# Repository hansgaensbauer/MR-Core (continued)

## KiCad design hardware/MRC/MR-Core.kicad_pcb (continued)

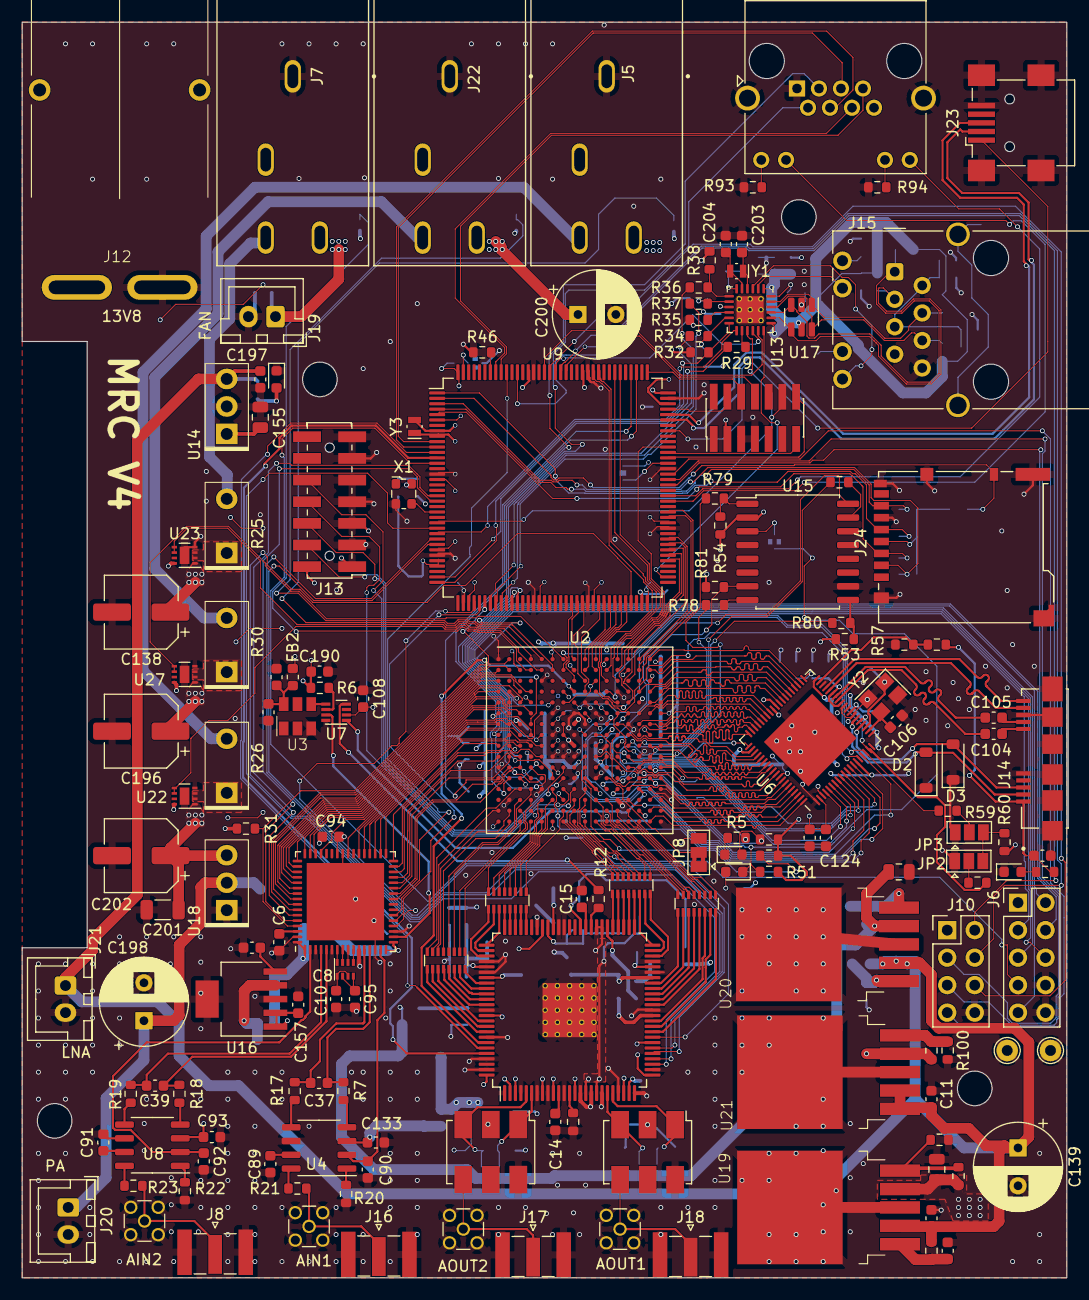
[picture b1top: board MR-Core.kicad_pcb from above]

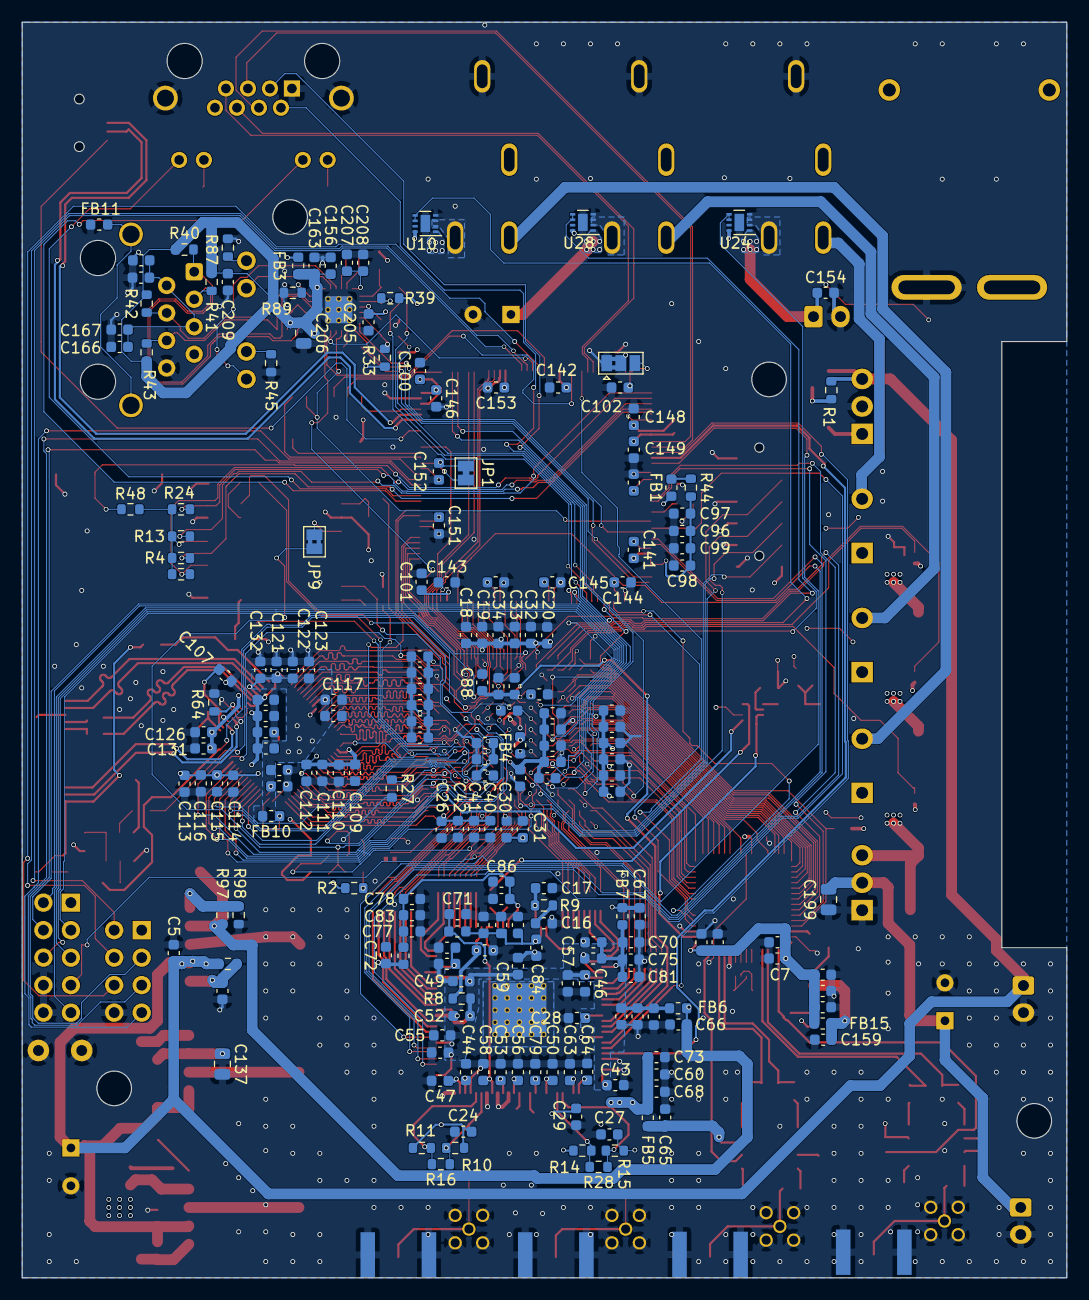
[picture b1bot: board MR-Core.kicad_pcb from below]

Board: 4 copper layers, 96.5 x 116.0 mm, 360 parts (203 on the bottom side), 377 nets.

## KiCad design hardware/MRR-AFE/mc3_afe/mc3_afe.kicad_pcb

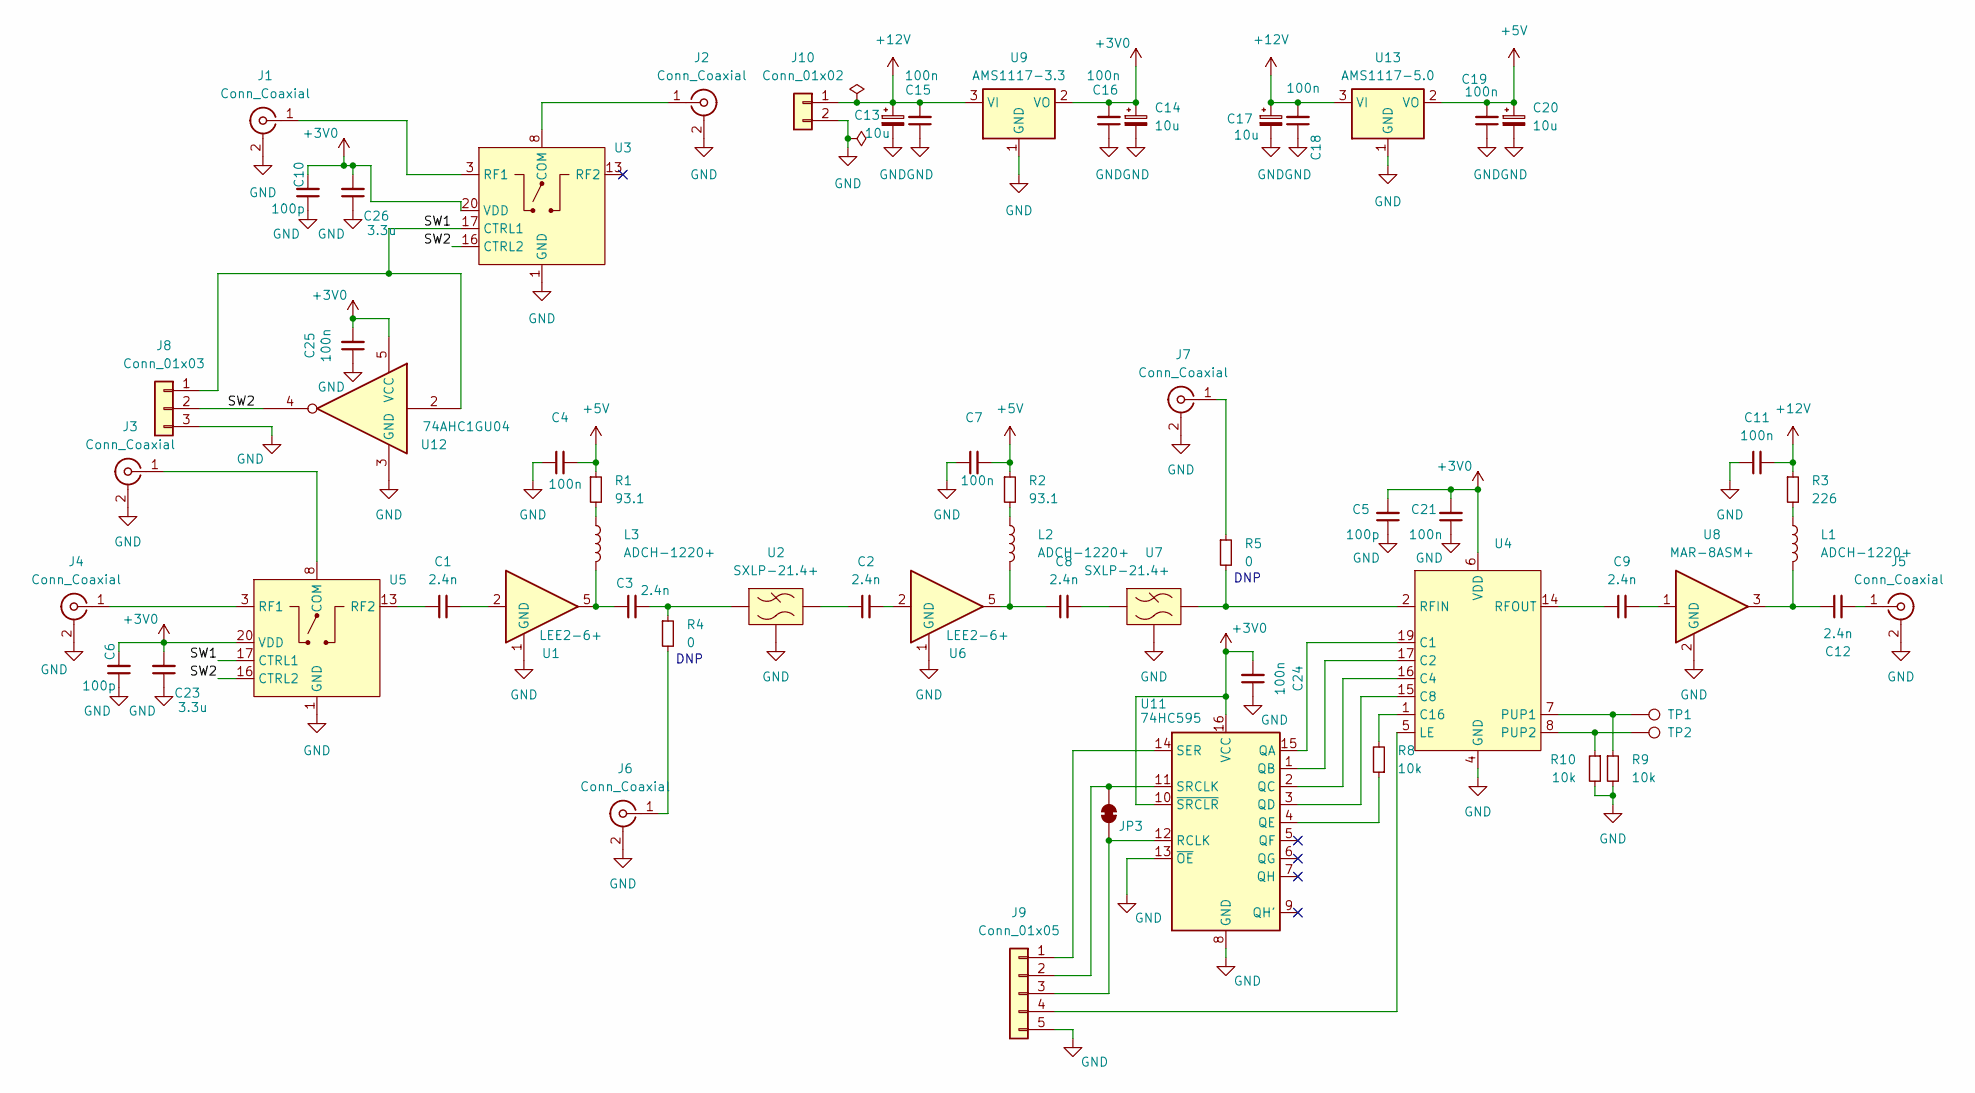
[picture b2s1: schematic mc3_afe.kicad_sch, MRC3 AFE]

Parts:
C1, C2, C3, C8, C9, C12: 2.4n; C_0805_2012Metric
C4, C7, C11, C21: 100n; C_0805_2012Metric
C5, C6, C10: 100p; C_0603_1608Metric
C13, C14, C17, C20: 10u; C_1206_3216Metric
C15, C16, C18, C19, C24, C25: 100n; C_0603_1608Metric
C23, C26: 3.3u; C_1206_3216Metric
J1, J3, J4, J6, J7: Conn_Coaxial; SMA_Samtec_SMA-J-P-H-ST-EM1_EdgeMount
J2, J5: Conn_Coaxial; MMCX_Molex_73415-1471_Vertical
J8: Conn_01x03; PinHeader_1x03_P2.54mm_Vertical
J9: Conn_01x05; PinHeader_1x05_P2.54mm_Vertical
J10: Conn_01x02; PinHeader_1x02_P2.54mm_Vertical
JP3: SolderJumper_2_Bridged; SolderJumper-2_P1.3mm_Bridged_Pad1.0x1.5mm
L1, L2, L3: ADCH-1220+; Mini-Circuits_CD637_H5.23mm
R1, R2: 93.1; R_0402_1005Metric
R3: 226; R_1206_3216Metric
R4, R5: 0; R_0402_1005Metric
R8, R9, R10: 10k; R_0603_1608Metric
TP1, TP2: TestPoint; TestPoint_THTPad_D1.0mm_Drill0.5mm
U1, U6: LEE2-6+; Mini-Circuits_FG873
U2, U7: SXLP-21.4+; Mini-Circuits_HF1139_LandPatternPL-230
U3, U4, U5: TQFN-20-1EP_4x4mm_P0.5mm_EP2.1x2.1mm
U8: MAR-8ASM+; Mini-Circuits_WW107
U9: AMS1117-3.3; SOT-223-3_TabPin2
U11: 74HC595; DHVQFN-16-1EP_2.5x3.5mm_P0.5mm_EP1x2mm; MPN SN74HCS595
U12: 74AHC1GU04; SOT-353_SC-70-5; MPN MC74VHC1GT04DFT1G
U13: AMS1117-5.0; SOT-223-3_TabPin2

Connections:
+3V0: C5.2, C6.2, C10.2, C14.1, C16.2, C21.2, C23.2, C24.2, C25.2, C26.2, U3.20 (VDD), U4.6 (VDD), U4.9 (VDD), U5.20 (VDD), U9.2 (VO), U11.10 (~SRCLR), U11.16 (VCC), U12.5 (VCC)
+5V: C4.2, C7.2, C19.2, C20.1, R1.1, R2.1, U13.2 (VO)
+12V: C11.2, C13.1, C15.2, C17.1, C18.2, J10.1, R3.1, U9.3 (VI), U13.3 (VI)
/SW1: J8.1, U3.17 (CTRL1), U5.17 (CTRL1), U12.2
/SW2: J8.2, U3.16 (CTRL2), U5.16 (CTRL2), U12.4
GND: C4.1, C5.1, C6.1, C7.1, C10.1, C11.1, C13.2, C14.2, C15.1, C16.1, C17.2, C18.1, C19.1, C20.2, C21.1, C23.1, C24.1, C25.1, C26.1, J1.2 (Ext), J2.2 (Ext), J3.2 (Ext), J4.2 (Ext), J5.2 (Ext), J6.2 (Ext), J7.2 (Ext), J8.3, J9.5, J10.2, R9.2, R10.2, U1.1 (GND), U1.3 (GND), U1.4 (GND), U1.6 (GND), U1.7 (GND), U2.2 (GND), U2.3 (GND), U2.4 (GND), U2.5 (GND), U2.6 (GND), U2.7 (GND), U3.1 (GND), U3.2 (GND), U3.4 (GND), U3.5 (GND), U3.6 (GND), U3.7 (GND), U3.9 (GND), U3.10 (GND), U3.11 (GND), U3.12 (GND), U3.14 (GND), U3.15 (GND), U3.18 (GND), U3.19 (GND), U3.21 (GND), U4.4 (GND), U4.10 (GND), U4.11 (GND), U4.12 (GND), U4.13 (GND), U4.18 (GND), U4.21 (GND), U5.1 (GND), U5.2 (GND), U5.4 (GND), U5.5 (GND), U5.6 (GND), U5.7 (GND), U5.9 (GND), U5.10 (GND), U5.11 (GND), U5.12 (GND), U5.14 (GND), U5.15 (GND), U5.18 (GND), U5.19 (GND), U5.21 (GND), U6.1 (GND), U6.3 (GND), U6.4 (GND), U6.6 (GND), U6.7 (GND), U7.2 (GND), U7.3 (GND), U7.4 (GND), U7.5 (GND), U7.6 (GND), U7.7 (GND), U8.2 (GND), U8.4 (GND), U9.1 (GND), U11.8 (GND), U11.13 (~OE), U12.3 (GND), U13.1 (GND)
unnamed: C1.2, U1.2
unnamed: C2.1, U2.8
unnamed: C2.2, U6.2
unnamed: C3.2, R4.1, U2.1
unnamed: C8.2, U7.1
unnamed: C9.2, U8.1
unnamed: J1.1 (In), U3.3 (RF1)
unnamed: J2.1 (In), U3.8 (COM)
unnamed: J3.1 (In), U5.8 (COM)
unnamed: J4.1 (In), U5.3 (RF1)
unnamed: C12.2, J5.1 (In)
unnamed: J6.1 (In), R4.2
unnamed: J7.1 (In), R5.1
unnamed: J9.1, U11.14 (SER)
unnamed: J9.2, JP3.2 (B), U11.11 (SRCLK)
unnamed: J9.3, JP3.1 (A), U11.12 (RCLK)
unnamed: J9.4, U4.5 (LE)
unnamed: L1.4 (RFGND), R3.2
unnamed: C12.1, L1.1 (RFIN), U8.3
unnamed: L2.4 (RFGND), R2.2
unnamed: C8.1, L2.1 (RFIN), U6.5
unnamed: L3.4 (RFGND), R1.2
unnamed: C3.1, L3.1 (RFIN), U1.5
unnamed: R8.2, U4.1 (C16)
unnamed: R9.1, TP1.1, U4.7 (PUP1)
unnamed: R10.1, TP2.1, U4.8 (PUP2)
unnamed: R5.2, U4.2 (RFIN), U7.8
unnamed: C9.1, U4.14 (RFOUT)
unnamed: C1.1, U5.13 (RF2)
unnamed: U4.19 (C1), U11.15 (QA)
unnamed: U4.17 (C2), U11.1 (QB)
unnamed: U4.16 (C4), U11.2 (QC)
unnamed: U4.15 (C8), U11.3 (QD)
unnamed: R8.1, U11.4 (QE)

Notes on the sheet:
DNP

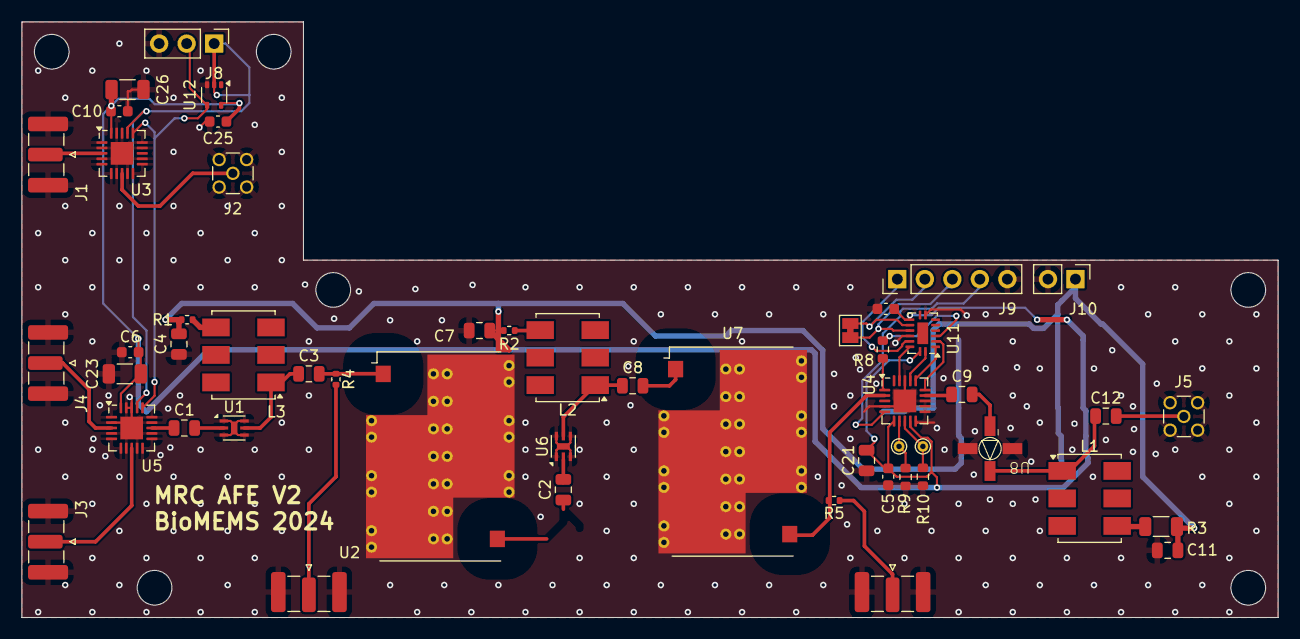
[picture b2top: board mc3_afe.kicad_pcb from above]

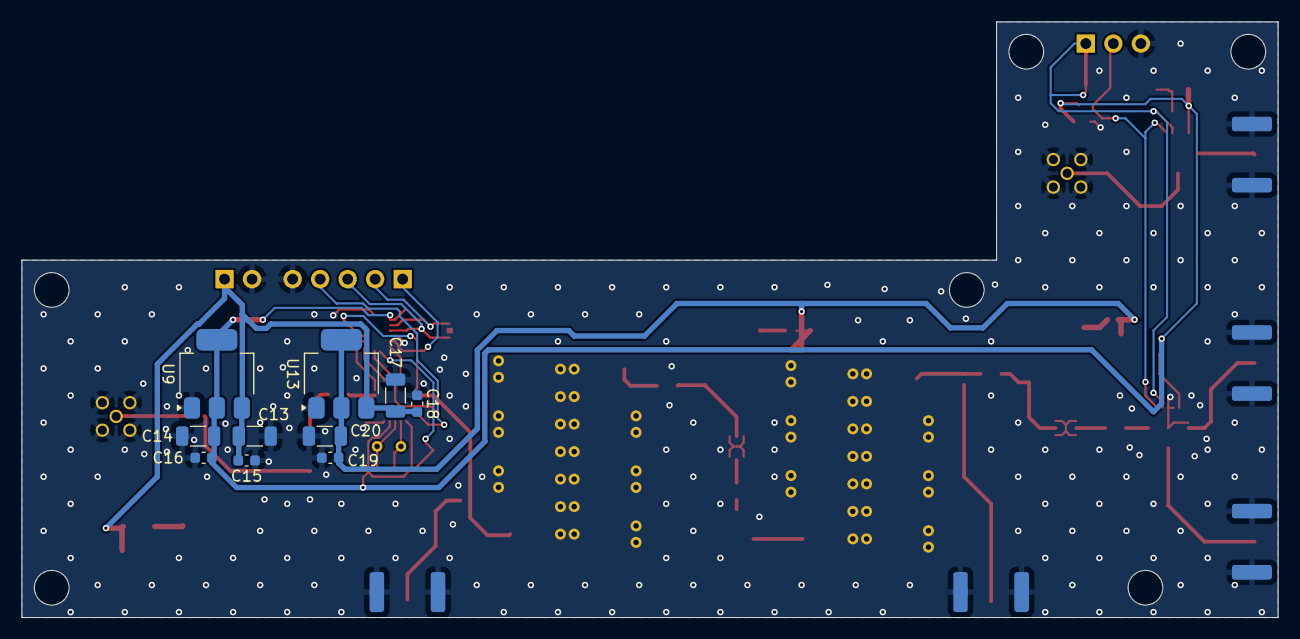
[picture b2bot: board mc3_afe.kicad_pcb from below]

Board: 4 copper layers, 116.0 x 55.0 mm, 61 parts (10 on the bottom side), 40 nets.

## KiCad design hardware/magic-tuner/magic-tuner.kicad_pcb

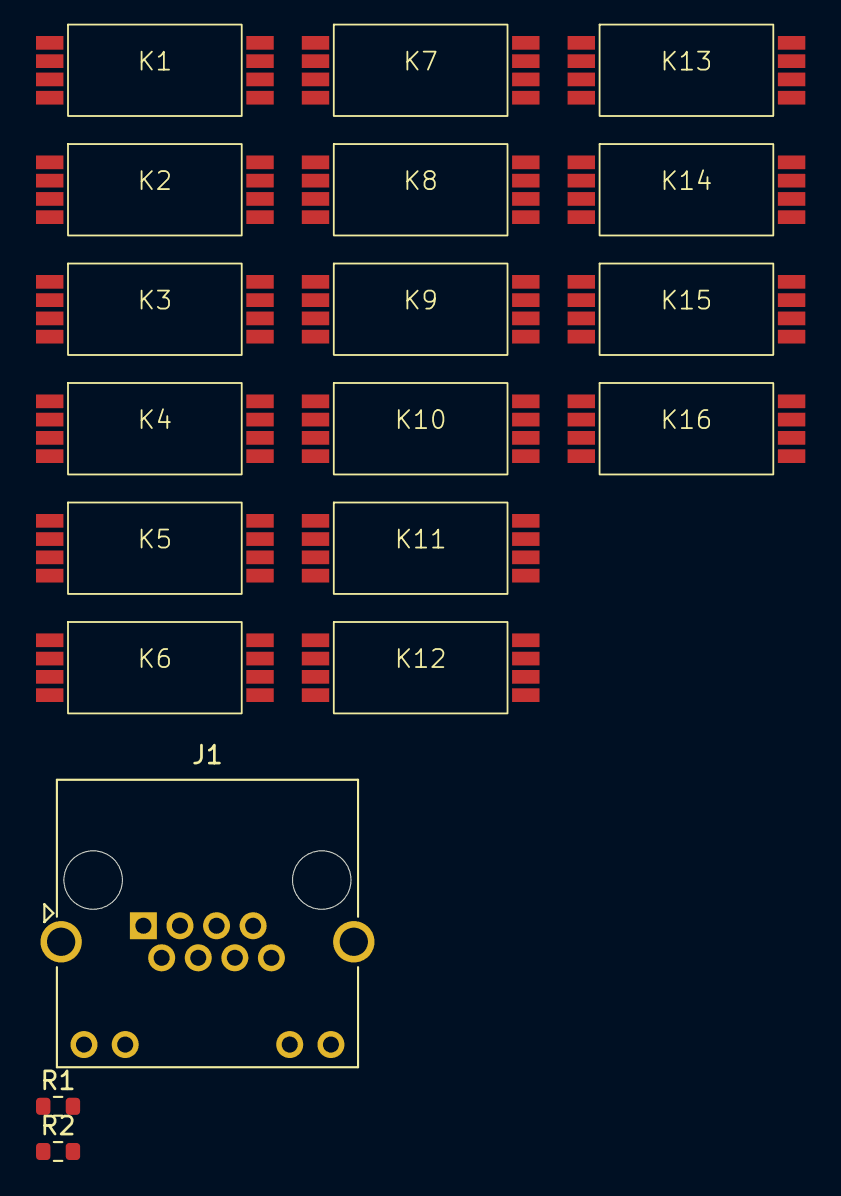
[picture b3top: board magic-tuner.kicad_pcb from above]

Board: 2 copper layers, 19 parts (0 on the bottom side), 6 nets, no tracks yet.

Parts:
J1: RJ45_LED_Shielded; RJ45_Amphenol_RJHSE538X
K1, K2, K3, K4, K5, K6, K7, K8, K9, K10, K11, K12, K13, K14, K15, K16: 9814; 9814_Reed_Relay
R1, R2: 4.7k; R_0603_1608Metric

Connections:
/cap_bank/C1: K1.6, K2.6, K3.6, K4.6, K5.6, K6.6, K7.6, K8.6, K9.6, K10.6, K11.6, K12.6, K13.6, K14.6, K15.6, K16.6
/cap_bank/R+: K1.2, K2.2, K3.2, K4.2, K5.2, K6.2, K7.2, K8.2, K9.2, K10.2, K11.2, K12.2, K13.2, K14.2, K15.2, K16.2
/cap_bank/R-: K1.1, K2.1, K3.1, K4.1, K5.1, K6.1, K7.1, K8.1, K9.1, K10.1, K11.1, K12.1, K13.1, K14.1, K15.1, K16.1
GND: J1.1, J1.SH, K1.3 (SH), K1.4, K1.7, K1.8, K2.3 (SH), K2.4, K2.7, K2.8, K3.3 (SH), K3.4, K3.7, K3.8, K4.3 (SH), K4.4, K4.7, K4.8, K5.3 (SH), K5.4, K5.7, K5.8, K6.3 (SH), K6.4, K6.7, K6.8, K7.3 (SH), K7.4, K7.7, K7.8, K8.3 (SH), K8.4, K8.7, K8.8, K9.3 (SH), K9.4, K9.7, K9.8, K10.3 (SH), K10.4, K10.7, K10.8, K11.3 (SH), K11.4, K11.7, K11.8, K12.3 (SH), K12.4, K12.7, K12.8, K13.3 (SH), K13.4, K13.7, K13.8, K14.3 (SH), K14.4, K14.7, K14.8, K15.3 (SH), K15.4, K15.7, K15.8, K16.3 (SH), K16.4, K16.7, K16.8, R1.1, R2.1
unnamed: J1.9, R1.2
unnamed: J1.11, R2.2

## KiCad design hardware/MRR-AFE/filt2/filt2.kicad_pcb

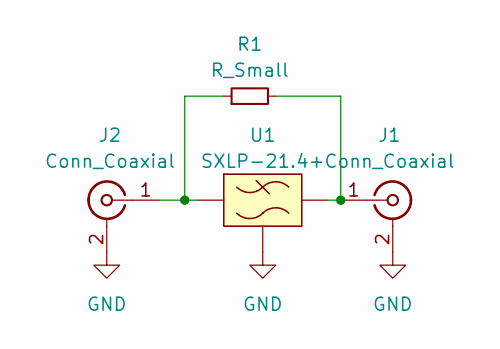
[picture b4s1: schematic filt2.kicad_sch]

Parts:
J1, J2: Conn_Coaxial; CONSMA013.062-Vertical
R1: R_Small; R_0603_1608Metric
U1: SXLP-21.4+; Mini-Circuits_HF1139_LandPatternPL-230_Truncated

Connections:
GND: J1.2 (Ext), J2.2 (Ext), U1.2 (GND), U1.3 (GND), U1.4 (GND), U1.5 (GND), U1.6 (GND), U1.7 (GND)
unnamed: J1.1 (In), R1.2, U1.8
unnamed: J2.1 (In), R1.1, U1.1

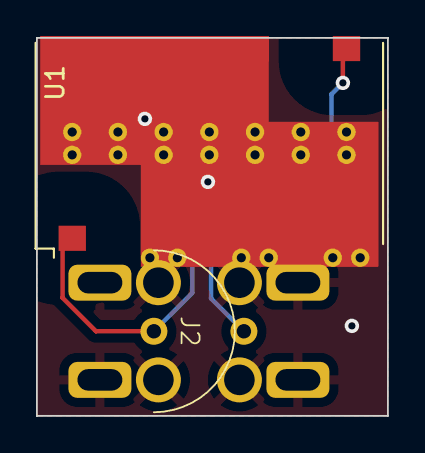
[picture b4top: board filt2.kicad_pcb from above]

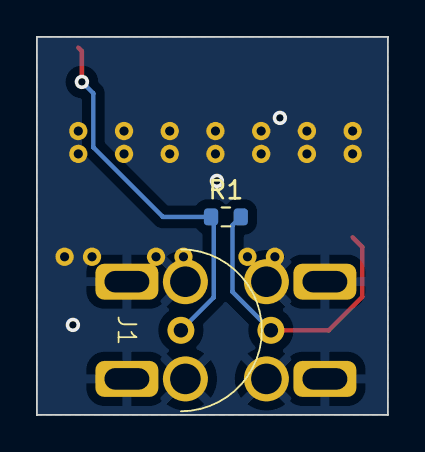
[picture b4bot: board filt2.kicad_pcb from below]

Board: 2 copper layers, 19.5 x 21.0 mm, 4 parts (2 on the bottom side), 3 nets.

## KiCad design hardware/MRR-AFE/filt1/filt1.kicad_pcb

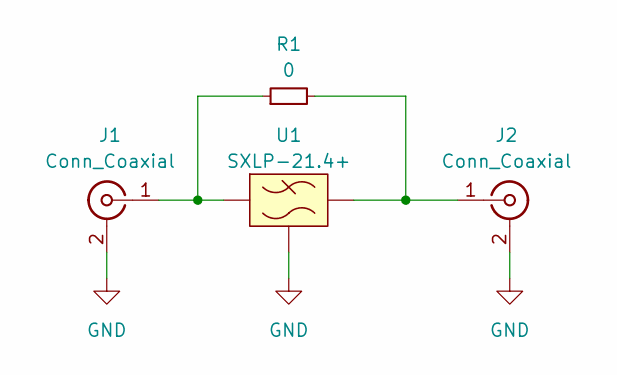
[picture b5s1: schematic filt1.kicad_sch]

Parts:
J1: Conn_Coaxial; CONSMA013.062-Vertical
J2: Conn_Coaxial; 538-73251-6521
R1: 0; R_0603_1608Metric
U1: SXLP-21.4+; Mini-Circuits_HF1139_LandPatternPL-230_Truncated

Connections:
GND: J1.2 (Ext), J2.2 (Ext), U1.2 (GND), U1.3 (GND), U1.4 (GND), U1.5 (GND), U1.6 (GND), U1.7 (GND)
unnamed: J1.1 (In), R1.1, U1.1
unnamed: J2.1 (In), R1.2, U1.8

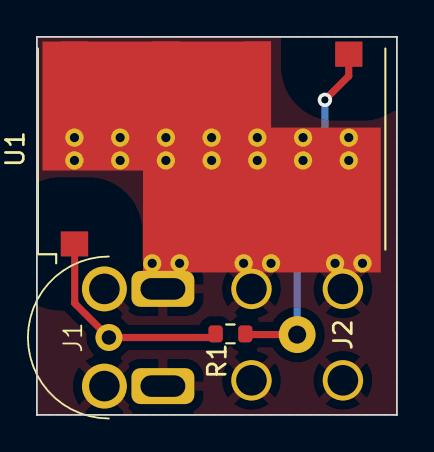
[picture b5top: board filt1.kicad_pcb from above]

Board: 2 copper layers, 20.0 x 21.0 mm, 4 parts (1 on the bottom side), 3 nets.

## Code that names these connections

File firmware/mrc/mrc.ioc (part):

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Mcu.Name=STM32F767ZITx
Mcu.Package=LQFP144
Mcu.UserName=STM32F767ZITx
PA11.Mode=Device_Only
PA11.Signal=USB_OTG_FS_DM
PA12.Mode=Device_Only
PA12.Signal=USB_OTG_FS_DP
PA4.GPIOParameters=GPIO_Label
PA4.GPIO_Label=ADC_SEN
PA4.Signal=GPIO_Output
PA5.Mode=Full_Duplex_Master
PA5.Signal=SPI1_SCK
PA6.Mode=Full_Duplex_Master
PA6.Signal=SPI1_MISO
PA9.Mode=Activate_VBUS
PA9.Signal=USB_OTG_FS_VBUS
PB1.GPIOParameters=GPIO_Label
PB1.GPIO_Label=FPGA_SEN
PB1.Signal=GPIO_Output
PB10.Mode=Full_Duplex_Master
PB10.Signal=SPI2_SCK
PB2.Mode=Simplex_Bidirectional_Master
PB2.Signal=SPI3_MOSI
PB5.Mode=Full_Duplex_Master
PB5.Signal=SPI1_MOSI
PB6.Mode=I2C
PB6.Signal=I2C1_SCL
PB7.Mode=I2C
PB7.Signal=I2C1_SDA
PC0.GPIOParameters=GPIO_Label
PC0.GPIO_Label=DAC_SEN
PC0.Signal=GPIO_Output
PC10.Mode=Simplex_Bidirectional_Master
PC10.Signal=SPI3_SCK
PC11.GPIOParameters=GPIO_Label
PC11.GPIO_Label=FIFO_FLAG
PC11.Signal=GPIO_Input
PC2.Mode=Full_Duplex_Master
PC2.Signal=SPI2_MISO
PC3.Mode=Full_Duplex_Master
PC3.Signal=SPI2_MOSI
PC6.Mode=Asynchronous
PC6.Signal=USART6_TX
PC7.Mode=Asynchronous
PC7.Signal=USART6_RX
PC8.Mode=NandChipSelect3_1
PC8.Signal=FMC_NCE
PD0.Signal=FMC_D2_DA2
PD1.Signal=FMC_D3_DA3
PD10.Signal=FMC_D15_DA15
PD11.Signal=FMC_A16_CLE
PD12.Signal=FMC_A17_ALE
PD14.Signal=FMC_D0_DA0
PD15.Signal=FMC_D1_DA1
PD4.Signal=FMC_NOE
PD5.Signal=FMC_NWE
PD8.Signal=FMC_D13_DA13
PD9.Signal=FMC_D14_DA14
PE10.Signal=FMC_D7_DA7
PE11.Signal=FMC_D8_DA8
PE12.Signal=FMC_D9_DA9
PE13.Signal=FMC_D10_DA10
PE14.Signal=FMC_D11_DA11
PE15.Signal=FMC_D12_DA12
PE2.Mode=Full_Duplex_Master
PE2.Signal=SPI4_SCK
PE5.Mode=Full_Duplex_Master
PE5.Signal=SPI4_MISO
PE6.Mode=Full_Duplex_Master
PE6.Signal=SPI4_MOSI
PE7.Signal=FMC_D4_DA4
PE8.Signal=FMC_D5_DA5
PE9.Signal=FMC_D6_DA6
PF0.GPIOParameters=GPIO_Label
PF0.GPIO_Label=MAG_IO0
PF0.Signal=GPIO_Output
PF1.GPIOParameters=GPIO_Label
PF1.GPIO_Label=MAG_IO1
PF1.Signal=GPIO_Output
PF2.GPIOParameters=GPIO_Label
PF2.GPIO_Label=DAC_NRST
PF2.Signal=GPIO_Output
PF3.GPIOParameters=GPIO_Label
PF3.GPIO_Label=DAC_SLEEP
PF3.Signal=GPIO_Output
PF4.GPIOParameters=GPIO_Label
PF4.GPIO_Label=DAC_TXEN
PF4.Signal=GPIO_Output
PF8.GPIOParameters=GPIO_Label
PF8.GPIO_Label=ADC_OF2
PF8.Signal=GPIO_Input
PF9.GPIOParameters=GPIO_Label
PF9.GPIO_Label=ADC_OF1
PF9.Signal=GPIO_Input
PG10.GPIOParameters=GPIO_Label
PG10.GPIO_Label=UCIO4
PG10.Signal=GPIO_Output
PG11.Signal=ETH_TX_EN
PG12.GPIOParameters=GPIO_Label
PG12.GPIO_Label=ATT_SRCLK
PG12.Signal=GPIO_Output
PG13.Signal=ETH_TXD0
PG3.GPIOParameters=GPIO_Label
PG3.GPIO_Label=MC_LED1
PG3.Signal=GPIO_Output
PG4.GPIOParameters=GPIO_Label
PG4.GPIO_Label=MC_LED2
PG4.Signal=GPIO_Output
PG6.GPIOParameters=GPIO_Label
PG6.GPIO_Label=UCIO0
PG6.Signal=GPIO_Output
PG7.GPIOParameters=GPIO_Label
PG7.GPIO_Label=ATT_SER
PG7.Signal=GPIO_Output
PG8.GPIOParameters=GPIO_Label
PG8.GPIO_Label=ATT_LE
PG8.Signal=GPIO_Output
PG9.GPIOParameters=GPIO_Label
PG9.GPIO_Label=UCIO3
PG9.Signal=GPIO_Output
PH0/OSC_IN.Mode=HSE-External-Clock-Source
PH0/OSC_IN.Signal=RCC_OSC_IN
PH1/OSC_OUT.Mode=HSE-External-Clock-Source
PH1/OSC_OUT.Signal=RCC_OSC_OUT
RCC.HSE_VALUE=50000000
RCC.SYSCLKFreq_VALUE=96000000
RCC.SYSCLKSource=RCC_SYSCLKSOURCE_PLLCLK
board=custom

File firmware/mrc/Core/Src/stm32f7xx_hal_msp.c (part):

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
    __HAL_RCC_GPIOB_CLK_ENABLE();
    /**I2C1 GPIO Configuration
    PB6     ------> I2C1_SCL
    PB7     ------> I2C1_SDA
    */
    GPIO_InitStruct.Pin = GPIO_PIN_6|GPIO_PIN_7;
    GPIO_InitStruct.Mode = GPIO_MODE_AF_OD;
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    __HAL_RCC_I2C1_CLK_DISABLE();

    /**I2C1 GPIO Configuration
    PB6     ------> I2C1_SCL
    PB7     ------> I2C1_SDA
    */
    HAL_GPIO_DeInit(GPIOB, GPIO_PIN_6);

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    __HAL_RCC_GPIOA_CLK_ENABLE();
    __HAL_RCC_GPIOB_CLK_ENABLE();
    /**SPI1 GPIO Configuration
    PA5     ------> SPI1_SCK
    PA6     ------> SPI1_MISO
    PB5     ------> SPI1_MOSI
    */
    GPIO_InitStruct.Pin = GPIO_PIN_5|GPIO_PIN_6;
    GPIO_InitStruct.Mode = GPIO_MODE_AF_PP;
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    __HAL_RCC_GPIOC_CLK_ENABLE();
    __HAL_RCC_GPIOB_CLK_ENABLE();
    /**SPI2 GPIO Configuration
    PC2     ------> SPI2_MISO
    PC3     ------> SPI2_MOSI
    PB10     ------> SPI2_SCK
    */
    GPIO_InitStruct.Pin = GPIO_PIN_2|GPIO_PIN_3;
    GPIO_InitStruct.Mode = GPIO_MODE_AF_PP;
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    __HAL_RCC_GPIOB_CLK_ENABLE();
    __HAL_RCC_GPIOC_CLK_ENABLE();
    /**SPI3 GPIO Configuration
    PB2     ------> SPI3_MOSI
    PC10     ------> SPI3_SCK
    */
    GPIO_InitStruct.Pin = GPIO_PIN_2;
    GPIO_InitStruct.Mode = GPIO_MODE_AF_PP;
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
    __HAL_RCC_GPIOE_CLK_ENABLE();
    /**SPI4 GPIO Configuration
    PE2     ------> SPI4_SCK
    PE5     ------> SPI4_MISO
    PE6     ------> SPI4_MOSI
    */
    GPIO_InitStruct.Pin = GPIO_PIN_2|GPIO_PIN_5|GPIO_PIN_6;
    GPIO_InitStruct.Mode = GPIO_MODE_AF_PP;
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    __HAL_RCC_SPI1_CLK_DISABLE();

    /**SPI1 GPIO Configuration
    PA5     ------> SPI1_SCK
    PA6     ------> SPI1_MISO
    PB5     ------> SPI1_MOSI
    */
    HAL_GPIO_DeInit(GPIOA, GPIO_PIN_5|GPIO_PIN_6);

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    __HAL_RCC_SPI2_CLK_DISABLE();

    /**SPI2 GPIO Configuration
    PC2     ------> SPI2_MISO
    PC3     ------> SPI2_MOSI
    PB10     ------> SPI2_SCK
    */
    HAL_GPIO_DeInit(GPIOC, GPIO_PIN_2|GPIO_PIN_3);

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    __HAL_RCC_SPI3_CLK_DISABLE();

    /**SPI3 GPIO Configuration
    PB2     ------> SPI3_MOSI
    PC10     ------> SPI3_SCK
    */
    HAL_GPIO_DeInit(GPIOB, GPIO_PIN_2);

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    __HAL_RCC_SPI4_CLK_DISABLE();

    /**SPI4 GPIO Configuration
    PE2     ------> SPI4_SCK
    PE5     ------> SPI4_MISO
    PE6     ------> SPI4_MOSI
    */
    HAL_GPIO_DeInit(GPIOE, GPIO_PIN_2|GPIO_PIN_5|GPIO_PIN_6);

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
    __HAL_RCC_GPIOC_CLK_ENABLE();
    /**USART6 GPIO Configuration
    PC6     ------> USART6_TX
    PC7     ------> USART6_RX
    */
    GPIO_InitStruct.Pin = GPIO_PIN_6|GPIO_PIN_7;
    GPIO_InitStruct.Mode = GPIO_MODE_AF_PP;
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    __HAL_RCC_USART6_CLK_DISABLE();

    /**USART6 GPIO Configuration
    PC6     ------> USART6_TX
    PC7     ------> USART6_RX
    */
    HAL_GPIO_DeInit(GPIOC, GPIO_PIN_6|GPIO_PIN_7);

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  __HAL_RCC_FMC_CLK_ENABLE();

  /** FMC GPIO Configuration
  PE7   ------> FMC_D4
  PE8   ------> FMC_D5
  PE9   ------> FMC_D6
  PE10   ------> FMC_D7
  PE11   ------> FMC_D8
  PE12   ------> FMC_D9
  PE13   ------> FMC_D10
  PE14   ------> FMC_D11
  PE15   ------> FMC_D12
  PD8   ------> FMC_D13
  PD9   ------> FMC_D14
  PD10   ------> FMC_D15
  PD11   ------> FMC_CLE
  PD12   ------> FMC_ALE
  PD14   ------> FMC_D0
  PD15   ------> FMC_D1
  PC8   ------> FMC_NCE
  PD0   ------> FMC_D2
  PD1   ------> FMC_D3
  PD4   ------> FMC_NOE
  PD5   ------> FMC_NWE
  */
  GPIO_InitStruct.Pin = GPIO_PIN_7|GPIO_PIN_8|GPIO_PIN_9|GPIO_PIN_10
                          |GPIO_PIN_11|GPIO_PIN_12|GPIO_PIN_13|GPIO_PIN_14
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  __HAL_RCC_FMC_CLK_DISABLE();

  /** FMC GPIO Configuration
  PE7   ------> FMC_D4
  PE8   ------> FMC_D5
  PE9   ------> FMC_D6
  PE10   ------> FMC_D7
  PE11   ------> FMC_D8
  PE12   ------> FMC_D9
  PE13   ------> FMC_D10
  PE14   ------> FMC_D11
  PE15   ------> FMC_D12
  PD8   ------> FMC_D13
  PD9   ------> FMC_D14
  PD10   ------> FMC_D15
  PD11   ------> FMC_CLE
  PD12   ------> FMC_ALE
  PD14   ------> FMC_D0
  PD15   ------> FMC_D1
  PC8   ------> FMC_NCE
  PD0   ------> FMC_D2
  PD1   ------> FMC_D3
  PD4   ------> FMC_NOE
  PD5   ------> FMC_NWE
  */
  HAL_GPIO_DeInit(GPIOE, GPIO_PIN_7|GPIO_PIN_8|GPIO_PIN_9|GPIO_PIN_10
                          |GPIO_PIN_11|GPIO_PIN_12|GPIO_PIN_13|GPIO_PIN_14
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
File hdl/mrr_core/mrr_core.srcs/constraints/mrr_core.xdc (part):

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
set_property -dict {PACKAGE_PIN N14 IOSTANDARD LVCMOS33} [get_ports FPGA_CLK]

set_property -dict { PACKAGE_PIN F5 IOSTANDARD LVCMOS18 } [get_ports { ADC_CLKOUT }]
set_property -dict { PACKAGE_PIN L3 IOSTANDARD LVCMOS18 } [get_ports { ADC_DA[0] }]
set_property -dict { PACKAGE_PIN L2 IOSTANDARD LVCMOS18 } [get_ports { ADC_DA[1] }]
set_property -dict { PACKAGE_PIN K2 IOSTANDARD LVCMOS18 } [get_ports { ADC_DA[2] }]
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set_property -dict { PACKAGE_PIN R2 IOSTANDARD LVCMOS33 } [get_ports { DAC_DB[13] }]
set_property -dict { PACKAGE_PIN R1 IOSTANDARD LVCMOS33 } [get_ports { DAC_DB[14] }]
set_property -dict { PACKAGE_PIN N3 IOSTANDARD LVCMOS33 } [get_ports { DAC_DB[15] }]
set_property -dict { PACKAGE_PIN D8 IOSTANDARD LVCMOS33 } [get_ports { DAC_PHSTR }]

set_property -dict { PACKAGE_PIN M2 IOSTANDARD LVCMOS33 } [get_ports { SCK }]
set_property -dict { PACKAGE_PIN L4 IOSTANDARD LVCMOS33 } [get_ports { SDI }]
set_property -dict { PACKAGE_PIN M1 IOSTANDARD LVCMOS33 } [get_ports { SDO }]
set_property -dict { PACKAGE_PIN L5 IOSTANDARD LVCMOS33 } [get_ports { SEN }]

set_property -dict { PACKAGE_PIN A14 IOSTANDARD LVCMOS33 } [get_ports { FMC_ALE }]
set_property -dict { PACKAGE_PIN C13 IOSTANDARD LVCMOS33 } [get_ports { FMC_CLE }]
set_property -dict { PACKAGE_PIN B12 IOSTANDARD LVCMOS33 } [get_ports { FMC_NCE }]
set_property -dict { PACKAGE_PIN B11 IOSTANDARD LVCMOS33 } [get_ports { FMC_NOE }]
set_property -dict { PACKAGE_PIN C11 IOSTANDARD LVCMOS33 } [get_ports { FMC_NWE }]
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set_property -dict { PACKAGE_PIN R15 IOSTANDARD LVCMOS33 } [get_ports { USB_DATA[29] }]
set_property -dict { PACKAGE_PIN R16 IOSTANDARD LVCMOS33 } [get_ports { USB_DATA[30] }]
set_property -dict { PACKAGE_PIN T15 IOSTANDARD LVCMOS33 } [get_ports { USB_DATA[31] }]
set_property -dict { PACKAGE_PIN N11 IOSTANDARD LVCMOS33 } [get_ports { USB_D_CLK }]
set_property -dict { PACKAGE_PIN D10 IOSTANDARD LVCMOS33 } [get_ports { USB_GPIO[0] }]
set_property -dict { PACKAGE_PIN D11 IOSTANDARD LVCMOS33 } [get_ports { USB_GPIO[1] }]
set_property -dict { PACKAGE_PIN G11 IOSTANDARD LVCMOS33 } [get_ports { USB_NOE }]
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
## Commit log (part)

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2025-08-21 Publish MR-Core
2025-11-11 well scanning, AFE
2025-11-11 fix compiler loop rolling
2025-11-24 first draft multi-interation loops
2025-11-25 Loop beyond 4096
2026-01-27 Update KiCAD Version, Integrate Libraries
2026-01-27 Add assembly guide
2026-01-27 Clean bill of materials
2026-01-28 Add License
2026-01-28 Move assembly instructions
2026-01-28 Fix Assembly.md Photo references
2026-02-16 Fix mrc_library md bug
